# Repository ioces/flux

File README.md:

# Flux - a battery powered soldering station for Weller RT tips

This design is currently a work in progress, with the ultimate goal of being a portable soldering station utilising Weller RT tips. The design has two outputs, and will be powered off regular 18 or 36 V power tool lithium ion battery packs. It will support all RT tips from the RTP, RTM at RTU series.

## Current status

Flux is still a work in progress, and has just made it to the PCA prototyping stage:

- [x] Design
- [x] Schematic capture
- [x] PCB layout of v1.0.0
- [x] Prototype PCB/stencil ordered
- [x] BOM generation
- [x] Part ordering
- [ ] Documentation
- [ ] Prototype assembly
- [ ] Firmware development
- [ ] Prototype testing
- [ ] Enclosure design

## License

This project is licensed under two separate licenses. The hardware design and documentation for this project is licensed under the [CERN Open Hardware Licence Version 2 - Strongly Reciprocal](https://ohwr.org/cern_ohl_s_v2.txt) (CERN-OHL-S-2.0). The software and firmware source code for the project is licensed under the [GNU General Public License Version 3](https://www.gnu.org/licenses/gpl-3.0.txt) (GPL-3.0-only).

Further details can be found in the [license file](LICENSE.md).

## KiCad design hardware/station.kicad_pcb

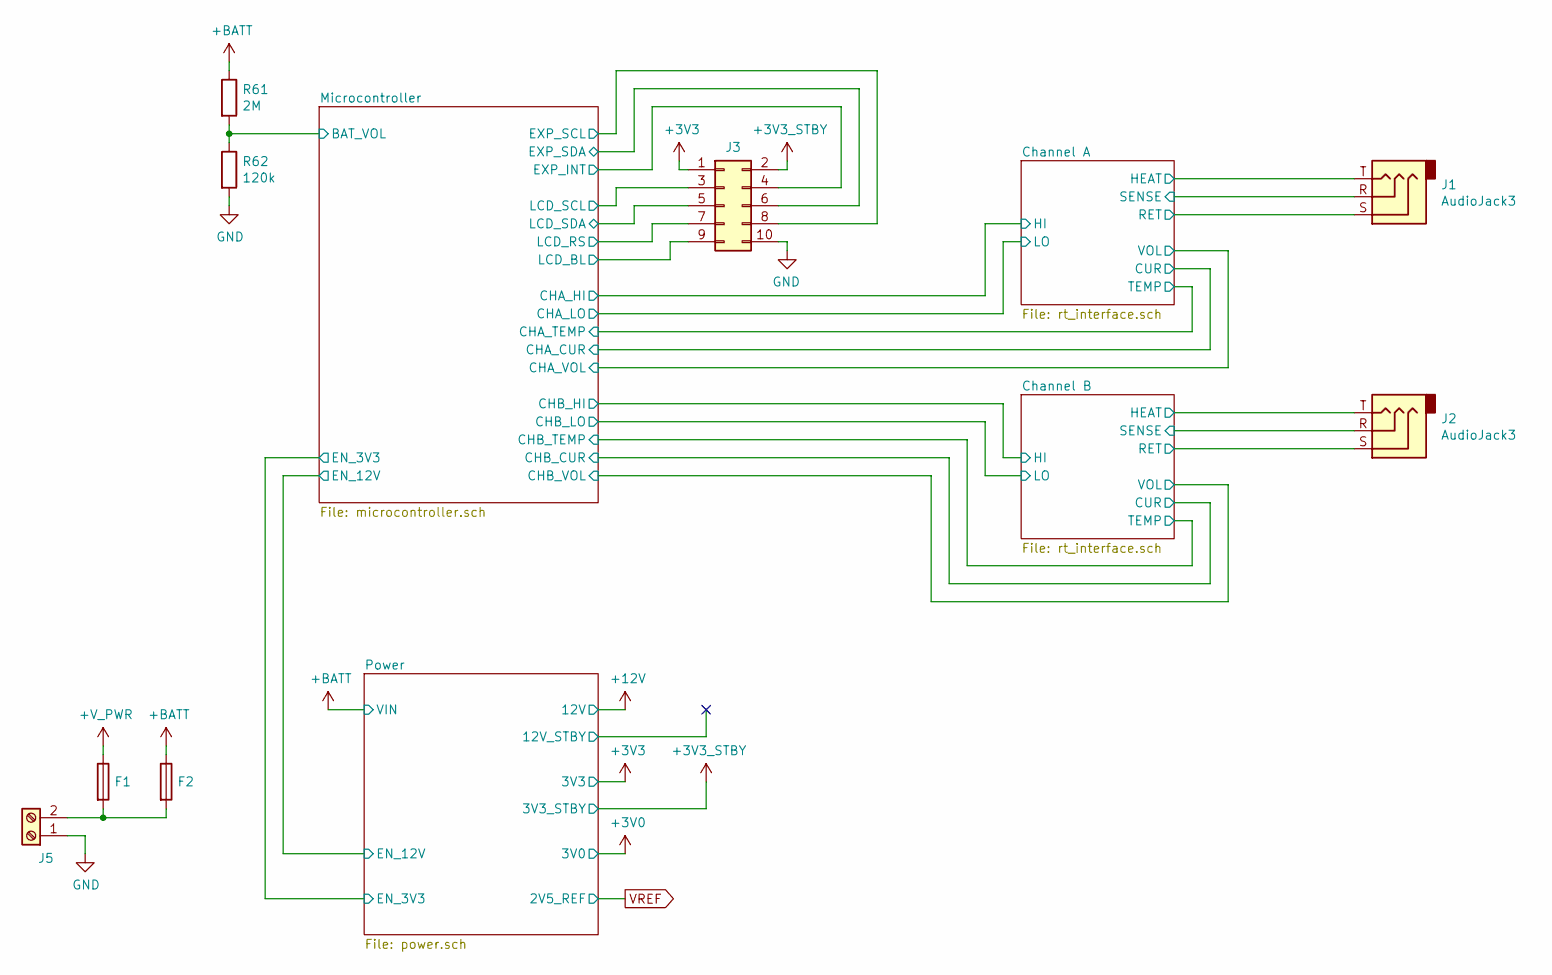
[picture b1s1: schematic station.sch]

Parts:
F1: Fuse; Fuse_2410; Part Number CB61F15A-TR2
F2: Fuse; Fuse_1206_3216Metric; Part Number C1F 375
J1, J2: AudioJack3; Jack_3.5mm_Adam_Tech_ASJ-125-3; Part Number ASJ-125-3
J3: Conn_02x05_Odd_Even; PinHeader_2x05_P2.54mm_BoardEdge; Part Number 10129382-910002BLF
J5: Screw_Terminal_01x02; TerminalBlock_bornier-2_P5.08mm; Part Number TB004-508-02BE
R61: 2M; R_0603_1608Metric; Tolerance 1%; Part Number ERJ-3EKF2004V
R62: 120k; R_0603_1608Metric; Tolerance 1%; Part Number RMCF0603FT120K

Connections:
+3V3: J3.1; also elsewhere on the board
+3V3_STBY: J3.2; also elsewhere on the board
+BATT: F2.1, R61.1; also elsewhere on the board
+V_PWR: F1.1; also elsewhere on the board
/Channel A/HEAT: J1.T; also elsewhere on the board
/Channel A/RET: J1.S; also elsewhere on the board
/Channel A/SENSE: J1.R; also elsewhere on the board
/Channel B/HEAT: J2.T; also elsewhere on the board
/Channel B/RET: J2.S; also elsewhere on the board
/Channel B/SENSE: J2.R; also elsewhere on the board
/Microcontroller/BAT_VOL: R61.2, R62.1; also elsewhere on the board
/Microcontroller/EXP_INT: J3.4; also elsewhere on the board
/Microcontroller/EXP_SCL: J3.8; also elsewhere on the board
/Microcontroller/EXP_SDA: J3.6; also elsewhere on the board
/Microcontroller/LCD_BL: J3.9; also elsewhere on the board
/Microcontroller/LCD_RS: J3.7; also elsewhere on the board
/Microcontroller/LCD_SCL: J3.3; also elsewhere on the board
/Microcontroller/LCD_SDA: J3.5; also elsewhere on the board
GND: J3.10, J5.1, R62.2; also elsewhere on the board
unnamed: F1.2, F2.2, J5.2

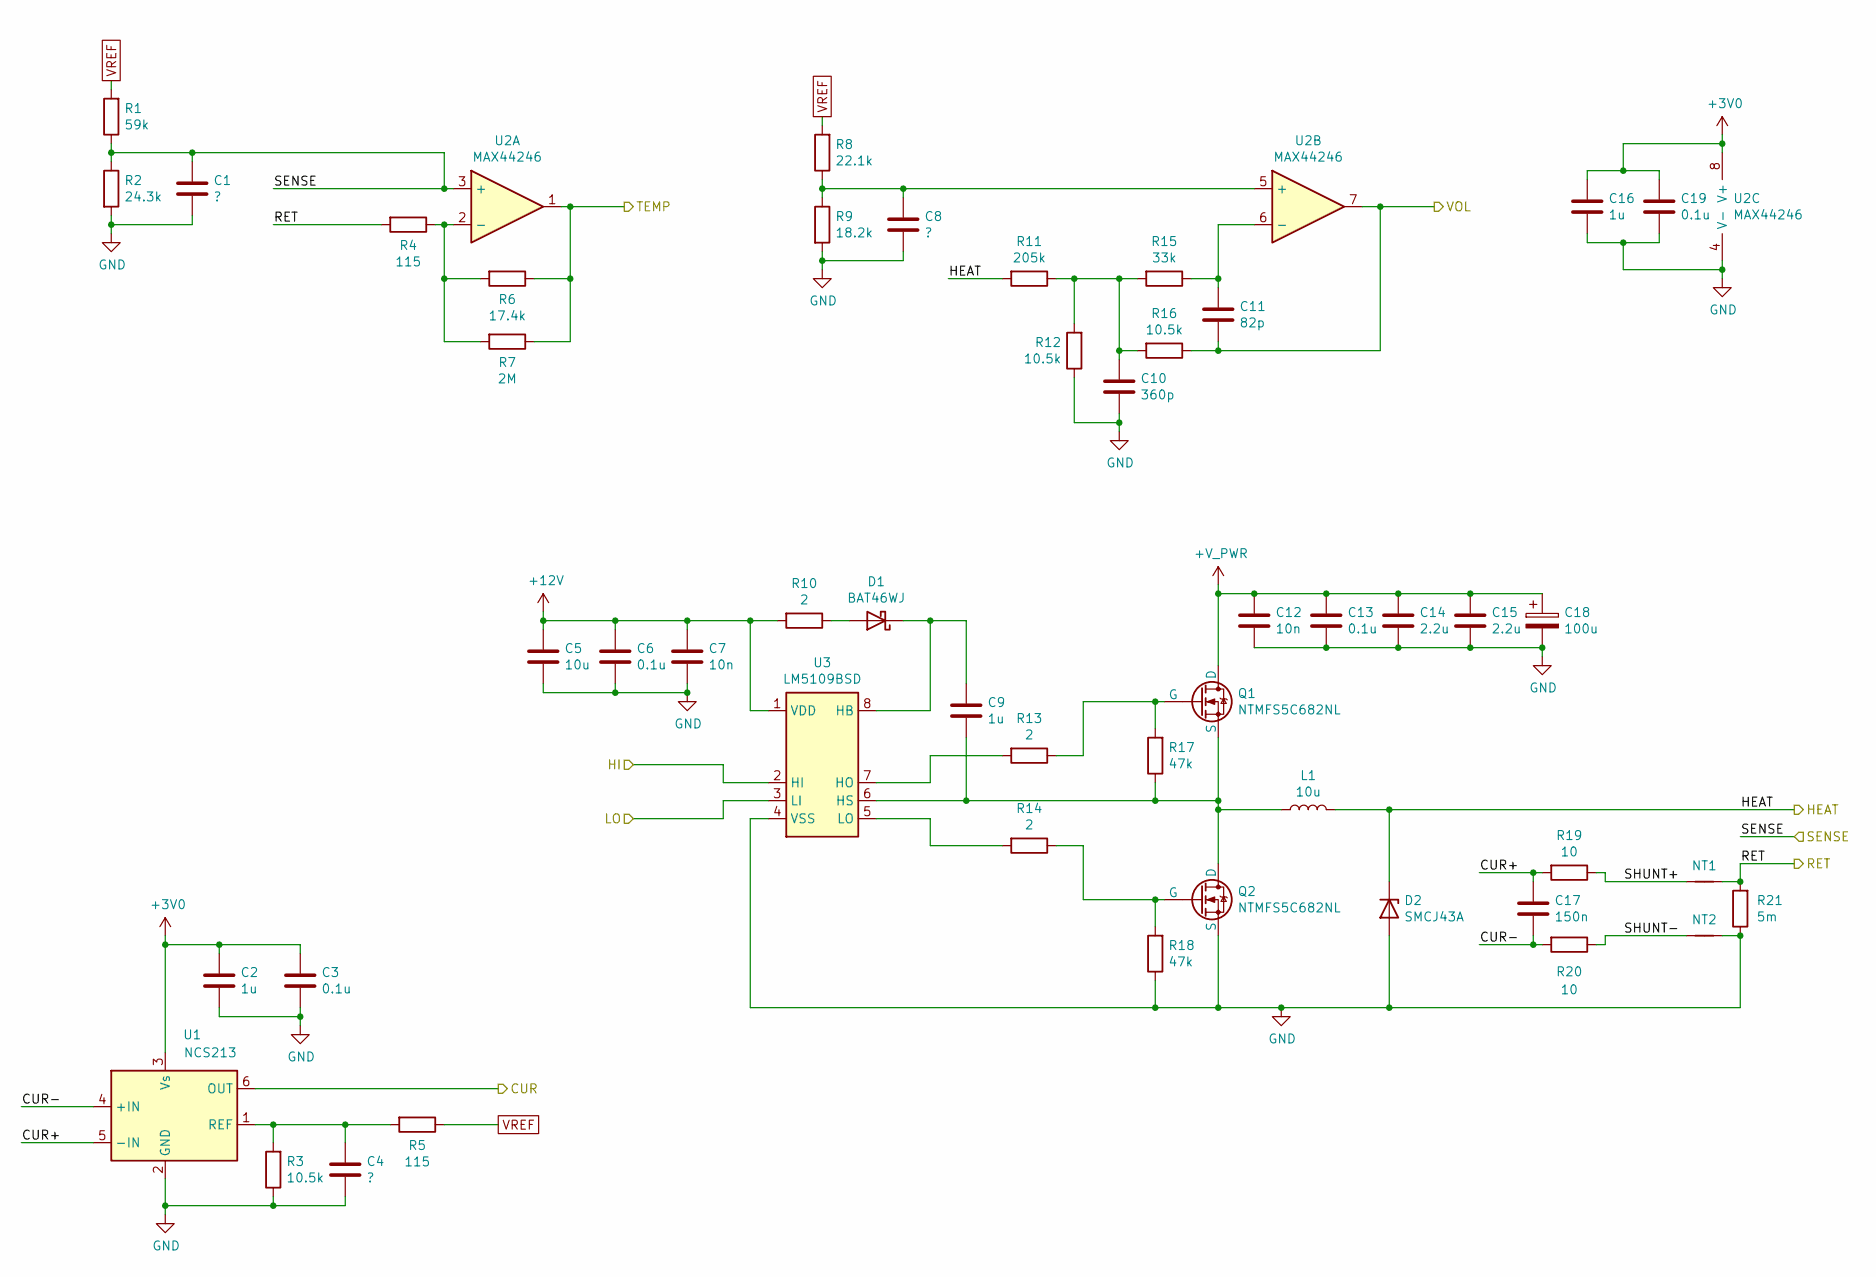
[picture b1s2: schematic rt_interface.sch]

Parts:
C1, C4, C8: ?; C_0805_2012Metric
C2, C9, C16: 1u; C_1206_3216Metric; Voltage Rating 25 V; Tolerance 10%; Part Number C1206C105K3RACAUTO
C3, C6, C19: 0.1u; C_0603_1608Metric; Voltage Rating 35 V; Tolerance 10%; Part Number GMK107B7104KAHT
C5: 10u; C_1206_3216Metric; Voltage Rating 35 V; Tolerance 10%; Part Number GMK316AB7106KL-TR
C7, C12: 10n; C_0603_1608Metric; Voltage Rating 100 V; Tolerance 10%; Part Number C1608X7R2A103K080AA
C10: 360p; C_0603_1608Metric; Voltage Rating 50 V; Tolerance 5%; Part Number C0603C361J5GAC7867
C11: 82p; C_0603_1608Metric; Voltage Rating 50 V; Tolerance 5%; Part Number C0603C820J5GACTU
C13: 0.1u; C_0805_2012Metric; Voltage Rating 100 V; Tolerance 10%; Part Number 885012207128
C14, C15: 2.2u; C_1210_3225Metric; Voltage Rating 100 V; Tolerance 10%; Part Number HMK325B7225KM-T
C17: 150n; C_0603_1608Metric; Voltage Rating 25 V; Tolerance 10%; Part Number 885012206072
C18: 100u; CP_Radial_D10.0mm_P5.00mm; Voltage Rating 63 V; Tolerance 20%; Part Number 63YXJ100M10X12.5
D1: BAT46WJ; D_SOD-323F; Part Number BAT46WJF
D2: SMCJ43A; D_SMC; Part Number SMCJ43A
L1: 10u; L_Bourns_SRP1265C; Part Number SRP1265C-100M
NT1, NT2: Net-Tie_2; NetTie-2_SMD_Pad0.2mm
Q1, Q2: NTMFS5C682NL; ONSemi_SO-8FL_488AA_Fill; Part Number NTMFS5C682NL
R1: 59k; R_0603_1608Metric; Tolerance 1%; Part Number RMCF0603FT59K0
R2: 24.3k; R_0603_1608Metric; Tolerance 1%; Part Number RMCF0603FT24K3
R3, R12, R16: 10.5k; R_0603_1608Metric; Tolerance 1%; Part Number RMCF0603FT10K5
R4, R5: 115; R_0603_1608Metric; Tolerance 1%; Part Number RMCF0603FT115R
R6: 17.4k; R_0603_1608Metric; Tolerance 1%; Part Number RMCF0603FT17K4
R7: 2M; R_0603_1608Metric; Tolerance 1%; Part Number ERJ-3EKF2004V
R8: 22.1k; R_0603_1608Metric; Tolerance 1%; Part Number RMCF0603FT22K1
R9: 18.2k; R_0603_1608Metric; Tolerance 1%; Part Number RMCF0603FT18K2
R10, R13, R14: 2; R_0603_1608Metric; Tolerance 5%; Part Number ERJ-PA3J2R0V
R11: 205k; R_0603_1608Metric; Tolerance 1%; Part Number RMCF0603FT205K
R15: 33k; R_0603_1608Metric; Tolerance 1%; Part Number CR0603-FX-3302ELF
R17, R18: 47k; R_0603_1608Metric; Tolerance 5%; Part Number CR0603-JW-473ELF
R19, R20: 10; R_0603_1608Metric; Tolerance 1%; Part Number CR0603-FX-10R0ELF
R21: 5m; R_0612_1632Metric; Tolerance 1%; Part Number CSRF0612FT5L00
U1: NCS213; SOT-363_SC-70-6; Part Number NCS213RSQT2G
U2: MAX44246; MSOP-8_3x3mm_P0.65mm; Part Number MAX44246AUA+
U3: LM5109BSD; WSON-8_4x4mm_P0.8mm; Part Number LM5109BSD/NOPB

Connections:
+3V0: C2.1, C3.1, C16.1, C19.1, U1.3 (Vs), U2.8 (V+); also elsewhere on the board
+12V: C5.1, C6.1, C7.1, R10.2, U3.1 (VDD); also elsewhere on the board
+V_PWR: C12.1, C13.1, C14.1, C15.1, C18.1, Q1.5 (D); also elsewhere on the board
/Channel A/CUR+: C17.1, R19.2, U1.5 (-IN)
/Channel A/CUR-: C17.2, R20.2, U1.4 (+IN)
/Channel A/HEAT: D2.1 (K), L1.2, R11.2; also elsewhere on the board
/Channel A/RET: NT1.2, R4.2, R21.2; also elsewhere on the board
/Channel A/SENSE: C1.2, R1.1, R2.1, U2.3 (+); also elsewhere on the board
/Channel A/SHUNT+: NT1.1, R19.1
/Channel A/SHUNT-: NT2.1, R20.1
/Microcontroller/CHA_CUR: U1.6 (OUT); also elsewhere on the board
/Microcontroller/CHA_HI: U3.2 (HI); also elsewhere on the board
/Microcontroller/CHA_LO: U3.3 (LI); also elsewhere on the board
/Microcontroller/CHA_TEMP: R6.1, R7.1, U2.1; also elsewhere on the board
/Microcontroller/CHA_VOL: C11.2, R16.1, U2.7; also elsewhere on the board
GND: C1.1, C2.2, C3.2, C4.1, C5.2, C6.2, C7.2, C8.1, C10.2, C12.2, C13.2, C14.2, C15.2, C16.2, C18.2, C19.2, D2.2 (A), NT2.2, Q2.1 (S), Q2.2 (S), Q2.3 (S), R2.2, R3.1, R9.2, R12.1, R18.1, R21.1, U1.2 (GND), U2.4 (V-), U3.4 (VSS), U3.9 (VSS); also elsewhere on the board
unnamed: C4.2, R3.2, R5.2, U1.1 (REF)
unnamed: C8.2, R8.1, R9.1, U2.5 (+)
unnamed: C9.1, L1.1, Q1.1 (S), Q1.2 (S), Q1.3 (S), Q2.5 (D), R17.1, U3.6 (HS)
unnamed: C9.2, D1.1 (K), U3.8 (HB)
unnamed: C10.1, R11.1, R12.2, R15.2, R16.2
unnamed: C11.1, R15.1, U2.6 (-)
unnamed: D1.2 (A), R10.1
unnamed: Q1.4 (G), R13.1, R17.2
unnamed: Q2.4 (G), R14.1, R18.2
unnamed: R4.1, R6.2, R7.2, U2.2 (-)
unnamed: R13.2, U3.7 (HO)
unnamed: R14.2, U3.5 (LO)
VREF: R1.2, R5.1, R8.2; also elsewhere on the board

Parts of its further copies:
C38, C41, C45: ?; C_0805_2012Metric
C39, C46, C53: 1u; C_1206_3216Metric; Voltage Rating 25 V; Tolerance 10%; Part Number C1206C105K3RACAUTO
C40, C43, C56: 0.1u; C_0603_1608Metric; Voltage Rating 35 V; Tolerance 10%; Part Number GMK107B7104KAHT
C42: 10u; C_1206_3216Metric; Voltage Rating 35 V; Tolerance 10%; Part Number GMK316AB7106KL-TR
C44, C49: 10n; C_0603_1608Metric; Voltage Rating 100 V; Tolerance 10%; Part Number C1608X7R2A103K080AA
C47: 360p; C_0603_1608Metric; Voltage Rating 50 V; Tolerance 5%; Part Number C0603C361J5GAC7867
C48: 82p; C_0603_1608Metric; Voltage Rating 50 V; Tolerance 5%; Part Number C0603C820J5GACTU
C50: 0.1u; C_0805_2012Metric; Voltage Rating 100 V; Tolerance 10%; Part Number 885012207128
C51, C52: 2.2u; C_1210_3225Metric; Voltage Rating 100 V; Tolerance 10%; Part Number HMK325B7225KM-T
C54: 150n; C_0603_1608Metric; Voltage Rating 25 V; Tolerance 10%; Part Number 885012206072
C55: 100u; CP_Radial_D10.0mm_P5.00mm; Voltage Rating 63 V; Tolerance 20%; Part Number 63YXJ100M10X12.5
D3: BAT46WJ; D_SOD-323F; Part Number BAT46WJF
D4: SMCJ43A; D_SMC; Part Number SMCJ43A
L4: 10u; L_Bourns_SRP1265C; Part Number SRP1265C-100M
NT3, NT4: Net-Tie_2; NetTie-2_SMD_Pad0.2mm
Q7, Q8: NTMFS5C682NL; ONSemi_SO-8FL_488AA_Fill; Part Number NTMFS5C682NL
R37: 59k; R_0603_1608Metric; Tolerance 1%; Part Number RMCF0603FT59K0
R38: 24.3k; R_0603_1608Metric; Tolerance 1%; Part Number RMCF0603FT24K3
R39, R48, R52: 10.5k; R_0603_1608Metric; Tolerance 1%; Part Number RMCF0603FT10K5
R40, R41: 115; R_0603_1608Metric; Tolerance 1%; Part Number RMCF0603FT115R
R42: 17.4k; R_0603_1608Metric; Tolerance 1%; Part Number RMCF0603FT17K4
R43: 2M; R_0603_1608Metric; Tolerance 1%; Part Number ERJ-3EKF2004V
R44: 22.1k; R_0603_1608Metric; Tolerance 1%; Part Number RMCF0603FT22K1
R45: 18.2k; R_0603_1608Metric; Tolerance 1%; Part Number RMCF0603FT18K2
R46, R49, R50: 2; R_0603_1608Metric; Tolerance 5%; Part Number ERJ-PA3J2R0V
R47: 205k; R_0603_1608Metric; Tolerance 1%; Part Number RMCF0603FT205K
R51: 33k; R_0603_1608Metric; Tolerance 1%; Part Number CR0603-FX-3302ELF
R53, R54: 47k; R_0603_1608Metric; Tolerance 5%; Part Number CR0603-JW-473ELF
R55, R56: 10; R_0603_1608Metric; Tolerance 1%; Part Number CR0603-FX-10R0ELF
R57: 5m; R_0612_1632Metric; Tolerance 1%; Part Number CSRF0612FT5L00
U8: NCS213; SOT-363_SC-70-6; Part Number NCS213RSQT2G
U9: MAX44246; MSOP-8_3x3mm_P0.65mm; Part Number MAX44246AUA+
U10: LM5109BSD; WSON-8_4x4mm_P0.8mm; Part Number LM5109BSD/NOPB

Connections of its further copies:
+3V0: C39.1, C40.1, C53.1, C56.1, U8.3 (Vs), U9.8 (V+); also elsewhere on the board
+12V: C42.1, C43.1, C44.1, R46.2, U10.1 (VDD); also elsewhere on the board
+V_PWR: C49.1, C50.1, C51.1, C52.1, C55.1, Q7.5 (D); also elsewhere on the board
/Channel B/CUR+: C54.1, R55.2, U8.5 (-IN)
/Channel B/CUR-: C54.2, R56.2, U8.4 (+IN)
/Channel B/HEAT: D4.1 (K), L4.2, R47.2; also elsewhere on the board
/Channel B/RET: NT3.2, R40.2, R57.2; also elsewhere on the board
/Channel B/SENSE: C38.2, R37.1, R38.1, U9.3 (+); also elsewhere on the board
/Channel B/SHUNT+: NT3.1, R55.1
/Channel B/SHUNT-: NT4.1, R56.1
/Microcontroller/CHB_CUR: U8.6 (OUT); also elsewhere on the board
/Microcontroller/CHB_HI: U10.2 (HI); also elsewhere on the board
/Microcontroller/CHB_LO: U10.3 (LI); also elsewhere on the board
/Microcontroller/CHB_TEMP: R42.1, R43.1, U9.1; also elsewhere on the board
/Microcontroller/CHB_VOL: C48.2, R52.1, U9.7; also elsewhere on the board
GND: C38.1, C39.2, C40.2, C41.1, C42.2, C43.2, C44.2, C45.1, C47.2, C49.2, C50.2, C51.2, C52.2, C53.2, C55.2, C56.2, D4.2 (A), NT4.2, Q8.1 (S), Q8.2 (S), Q8.3 (S), R38.2, R39.1, R45.2, R48.1, R54.1, R57.1, U8.2 (GND), U9.4 (V-), U10.4 (VSS), U10.9 (VSS); also elsewhere on the board
unnamed: C41.2, R39.2, R41.2, U8.1 (REF)
unnamed: C45.2, R44.1, R45.1, U9.5 (+)
unnamed: C46.1, L4.1, Q7.1 (S), Q7.2 (S), Q7.3 (S), Q8.5 (D), R53.1, U10.6 (HS)
unnamed: C46.2, D3.1 (K), U10.8 (HB)
unnamed: C47.1, R47.1, R48.2, R51.2, R52.2
unnamed: C48.1, R51.1, U9.6 (-)
unnamed: D3.2 (A), R46.1
unnamed: Q7.4 (G), R49.1, R53.2
unnamed: Q8.4 (G), R50.1, R54.2
unnamed: R40.1, R42.2, R43.2, U9.2 (-)
unnamed: R49.2, U10.7 (HO)
unnamed: R50.2, U10.5 (LO)
VREF: R37.2, R41.1, R44.2; also elsewhere on the board

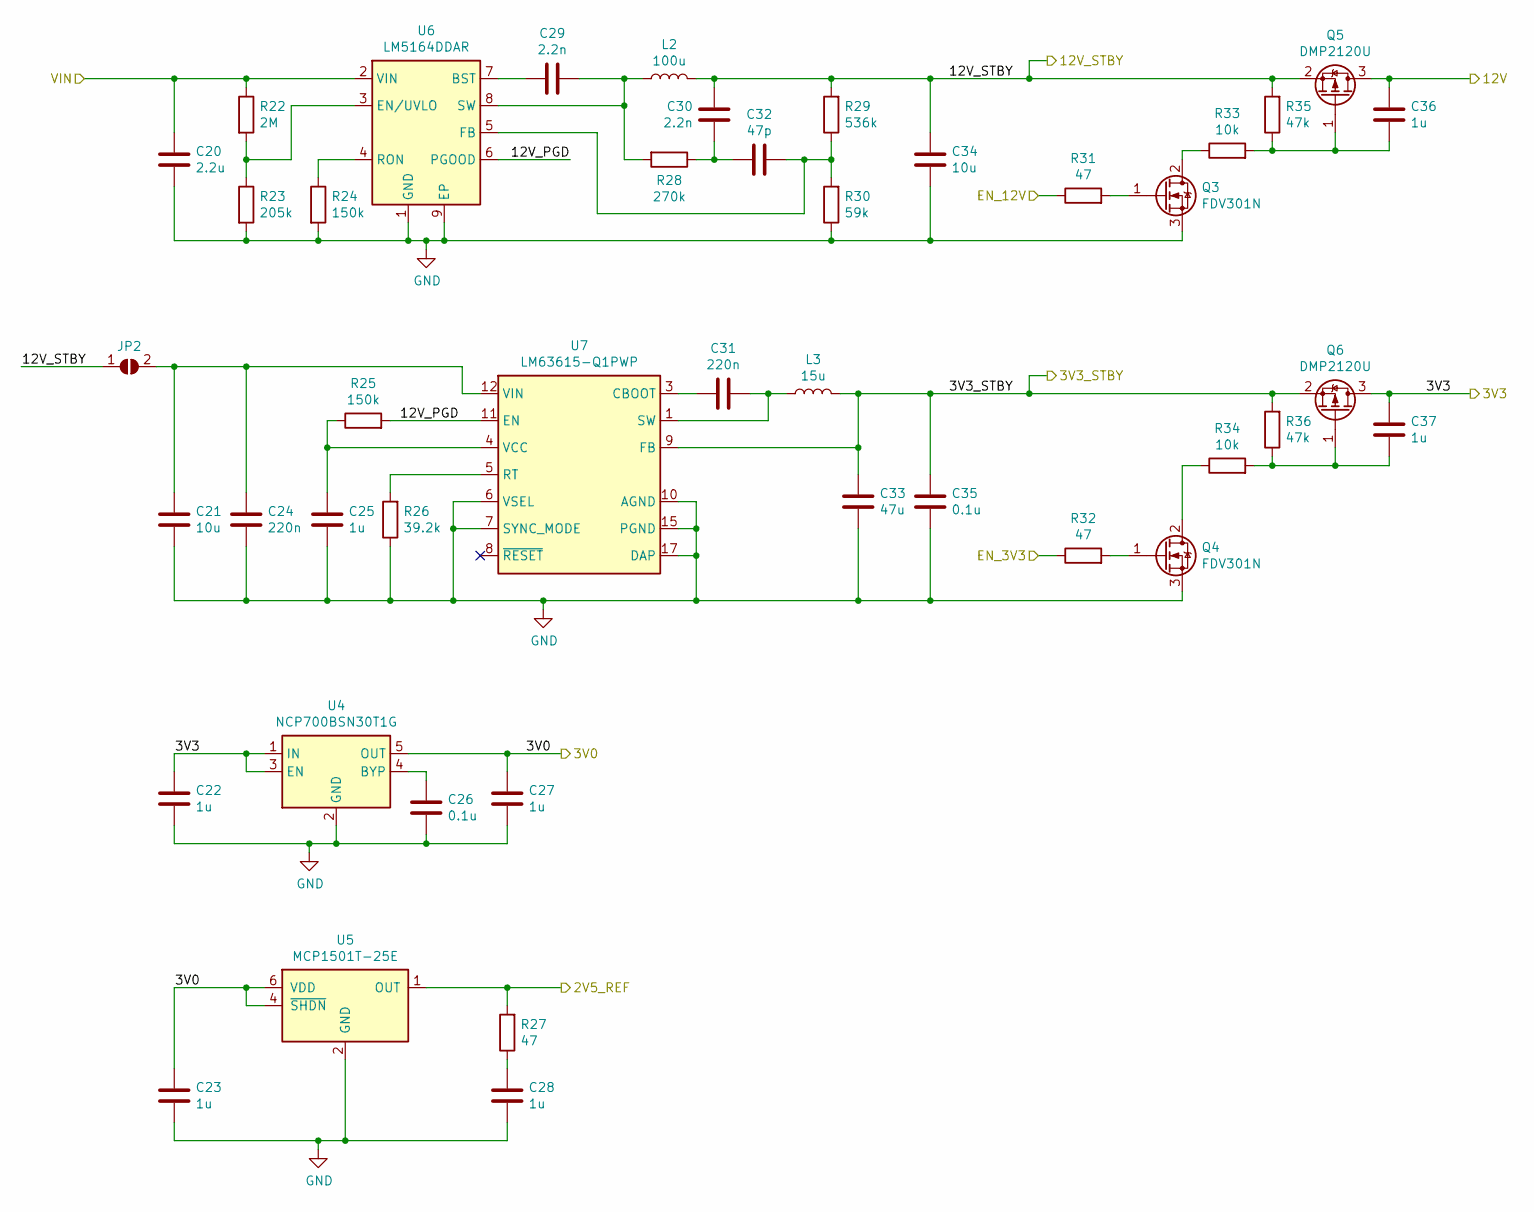
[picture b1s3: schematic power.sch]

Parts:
C20: 2.2u; C_1210_3225Metric; Voltage Rating 100 V; Tolerance 10%; Part Number HMK325B7225KM-T
C21, C34: 10u; C_1206_3216Metric; Voltage Rating 35 V; Tolerance 10%; Part Number GMK316AB7106KL-TR
C22, C23, C25, C27, C28, C36, C37: 1u; C_1206_3216Metric; Voltage Rating 25 V; Tolerance 10%; Part Number C1206C105K3RACAUTO
C24, C31: 220n; C_0603_1608Metric; Voltage Rating 50 V; Tolerance 10%; Part Number C1608X7R1H224K080AB
C26, C35: 0.1u; C_0603_1608Metric; Voltage Rating 35 V; Tolerance 10%; Part Number GMK107B7104KAHT
C29, C30: 2.2n; C_0805_2012Metric; Voltage Rating 50 V; Tolerance 10%; Part Number C0805C222K5RACTU
C32: 47p; C_0603_1608Metric; Tolerance 5%; Voltage Rating 16V; Part Number 885012006021
C33: 47u; C_1210_3225Metric; Voltage Rating 16 V; Tolerance 10%; Part Number GRM32EC81C476KE15K
JP2: SolderJumper_2_Open; SolderJumper-2_3A
L2: 100u; L_Coilcraft_MSS1210; Part Number MSS1210-104KEB
L3: 15u; L_TDK_SLF10165; Part Number SLF10165T-150M3R13PF
Q3, Q4: FDV301N; SOT-23; Part Number FDV301N
Q5, Q6: DMP2120U; SOT-23; Part Number DMP2120U
R22: 2M; R_0603_1608Metric; Tolerance 1%; Part Number ERJ-3EKF2004V
R23: 205k; R_0603_1608Metric; Tolerance 1%; Part Number RMCF0603FT205K
R24, R25: 150k; R_0603_1608Metric; Tolerance 1%; Part Number RMCF0603FT150K
R26: 39.2k; R_0603_1608Metric; Tolerance 1%; Part Number RMCF0603FT39K2
R27, R31, R32: 47; R_0603_1608Metric; Tolerance 1%; Part Number RMCF0603FT47R0
R28: 270k; R_0603_1608Metric; Tolerance 1%; Part Number RMCF0603FT270K
R29: 536k; R_0603_1608Metric; Tolerance 1%; Part Number RMCF0603FT536K
R30: 59k; R_0603_1608Metric; Tolerance 1%; Part Number RMCF0603FT59K0
R33, R34: 10k; R_0603_1608Metric; Tolerance 5%; Part Number RMCF0603JG10K0
R35, R36: 47k; R_0603_1608Metric; Tolerance 5%; Part Number CR0603-JW-473ELF
U4: NCP700BSN30T1G; SOT-23-5; Part Number NCP700BSN30T1G
U5: MCP1501T-25E; SOT-23-6; Part Number MCP1501T-25E/CHY
U6: LM5164DDAR; TI_SO-PowerPAD-8; Part Number LM5164DDAR
U7: LM63615-Q1PWP; HTSSOP-16-1EP_4.4x5mm_P0.65mm_EP3.4x5mm_Mask2.46x2.31mm; Part Number LM63615-Q1PWP

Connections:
+3V0: C23.1, C27.1, U4.5 (OUT), U5.4 (~SHDN), U5.6 (VDD); also elsewhere on the board
+3V3: C22.1, C37.1, Q6.3 (D), U4.1 (IN), U4.3 (EN); also elsewhere on the board
+3V3_STBY: C33.1, C35.1, L3.2, Q6.2 (S), R36.2, U7.9 (FB); also elsewhere on the board
+12V: C36.1, Q5.3 (D); also elsewhere on the board
+BATT: C20.1, R22.1, U6.2 (VIN); also elsewhere on the board
/Microcontroller/EN_3V3: R32.1; also elsewhere on the board
/Microcontroller/EN_12V: R31.1; also elsewhere on the board
/Power/12V_PGD: R25.2, U6.6 (PGOOD), U7.11 (EN)
/Power/12V_STBY: C30.2, C34.1, JP2.1 (A), L2.2, Q5.2 (S), R29.2, R35.2
GND: C20.2, C21.2, C22.2, C23.2, C24.2, C25.2, C26.2, C27.2, C28.2, C33.2, C34.2, C35.2, Q3.3 (S), Q4.3 (S), R23.2, R24.2, R26.1, R30.1, U4.2 (GND), U5.2 (GND), U5.3 (GND), U5.5 (GND), U6.1 (GND), U6.9 (EP), U7.6 (VSEL), U7.7 (SYNC_MODE), U7.10 (AGND), U7.15 (PGND), U7.16 (PGND), U7.17 (DAP); also elsewhere on the board
unnamed: C21.1, C24.1, JP2.2 (B), U7.12 (VIN), U7.13 (VIN)
unnamed: C25.1, R25.1, U7.4 (VCC)
unnamed: C26.1, U4.4 (BYP)
unnamed: C28.1, R27.1
unnamed: C29.1, L2.1, R28.2, U6.8 (SW)
unnamed: C29.2, U6.7 (BST)
unnamed: C30.1, C32.1, R28.1
unnamed: C31.1, L3.1, U7.1 (SW), U7.2 (SW)
unnamed: C31.2, U7.3 (CBOOT)
unnamed: C32.2, R29.1, R30.2, U6.5 (FB)
unnamed: C36.2, Q5.1 (G), R33.2, R35.1
unnamed: C37.2, Q6.1 (G), R34.2, R36.1
unnamed: Q3.1 (G), R31.2
unnamed: Q3.2 (D), R33.1
unnamed: Q4.1 (G), R32.2
unnamed: Q4.2 (D), R34.1
unnamed: R22.2, R23.1, U6.3 (EN/UVLO)
unnamed: R24.1, U6.4 (RON)
unnamed: R26.2, U7.5 (RT)
VREF: R27.2, U5.1 (OUT); also elsewhere on the board

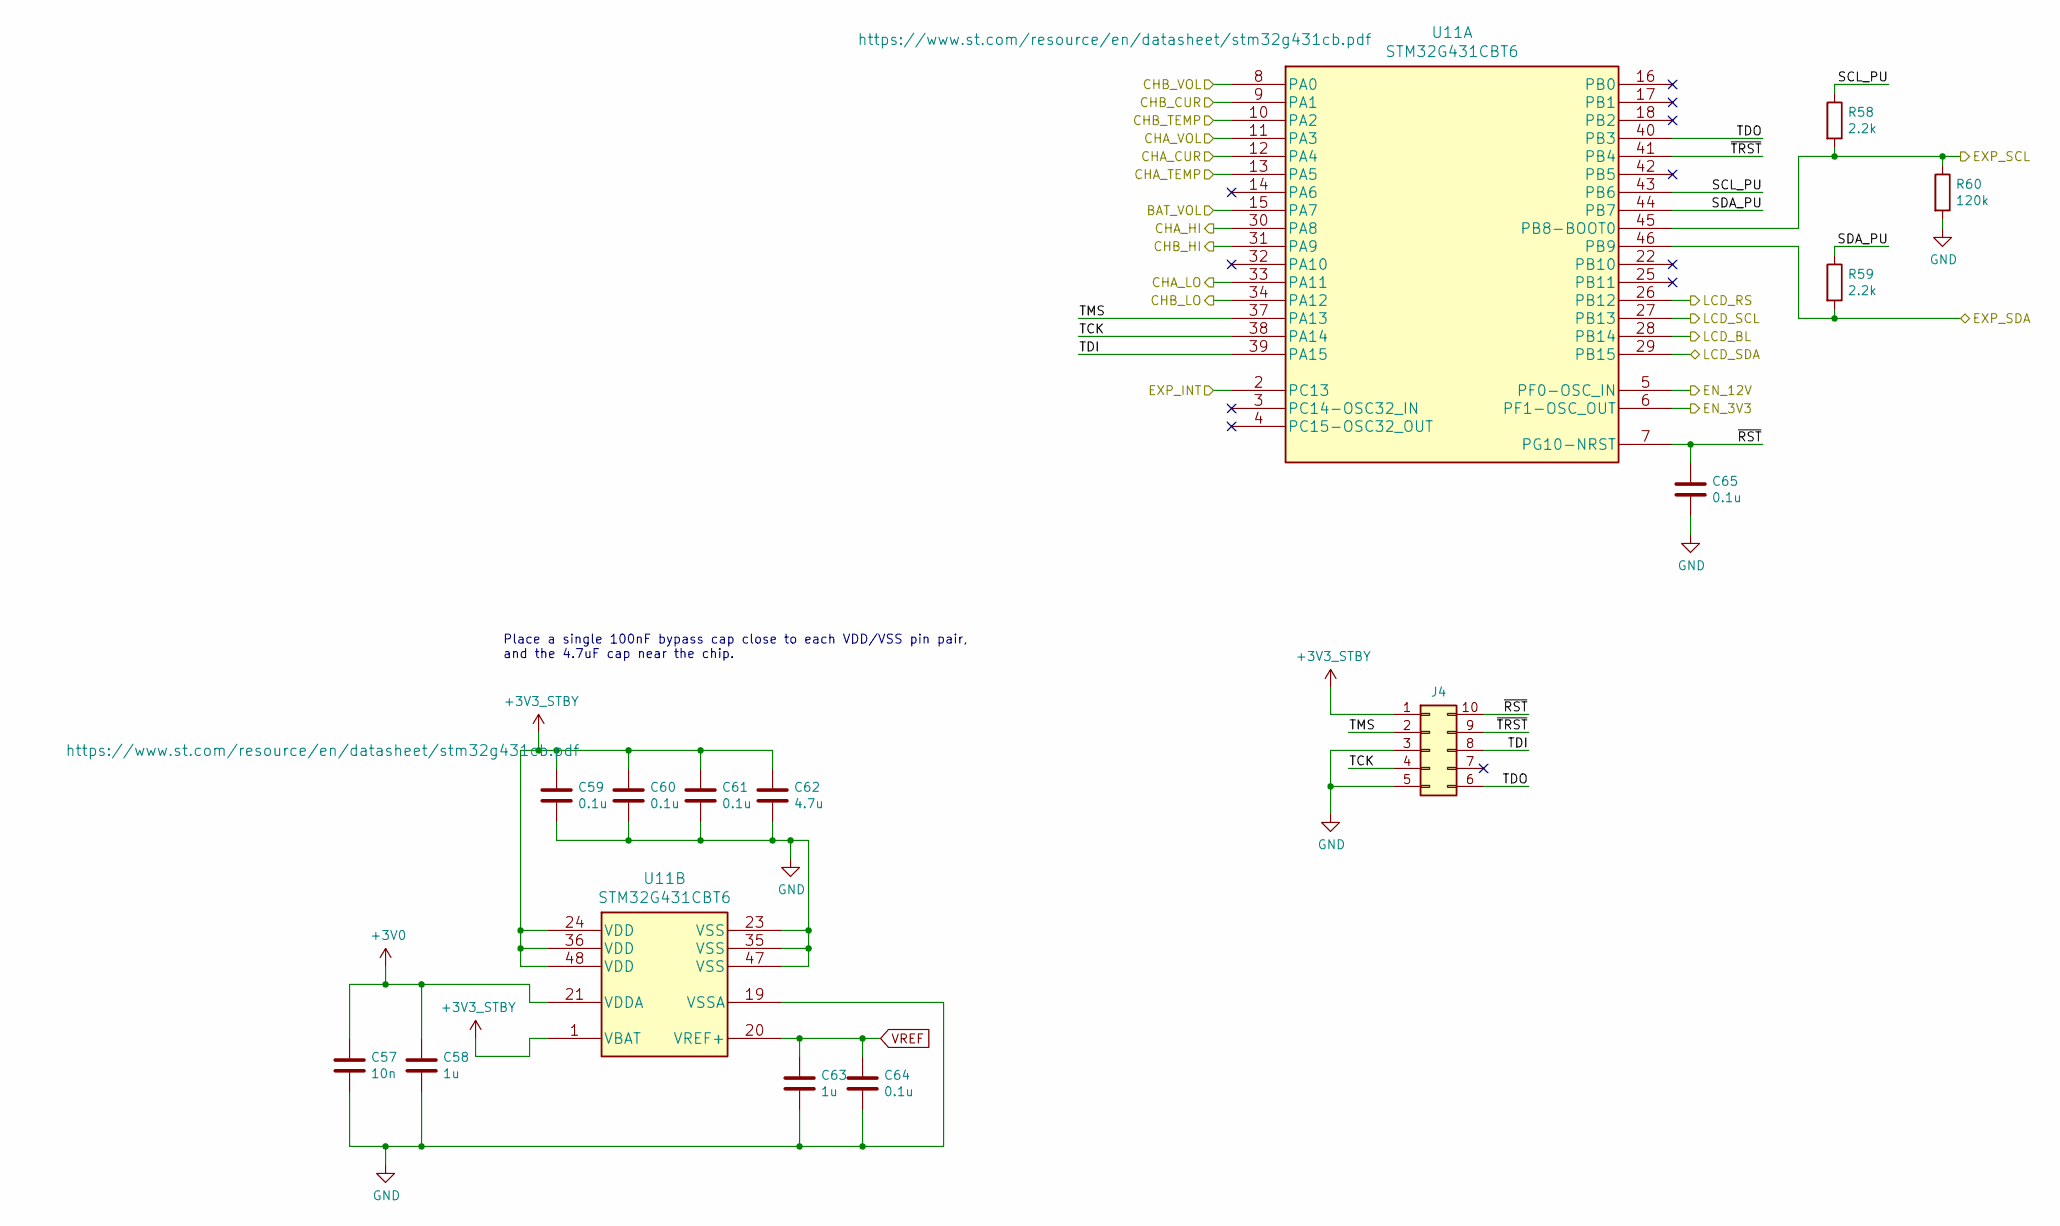
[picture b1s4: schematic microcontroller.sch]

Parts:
C57: 10n; C_0603_1608Metric; Voltage Rating 100 V; Tolerance 10%; Part Number C1608X7R2A103K080AA
C58, C63: 1u; C_1206_3216Metric; Voltage Rating 25 V; Tolerance 10%; Part Number C1206C105K3RACAUTO
C59, C60, C61, C64, C65: 0.1u; C_0603_1608Metric; Voltage Rating 35 V; Tolerance 10%; Part Number GMK107B7104KAHT
C62: 4.7u; C_1206_3216Metric; Voltage Rating 25 V; Tolerance 10%; Part Number CL31B475KAHNFNE
J4: Conn_02x05_Counter_Clockwise; Tag-Connect_TC2050-IDC-NL_2x05_P1.27mm_Vertical
R58, R59: 2.2k; R_0603_1608Metric; Tolerance 5%; Part Number RMCF0603JT2K20
R60: 120k; R_0603_1608Metric; Tolerance 1%; Part Number RMCF0603FT120K
U11: STM32G431CBT6; LQFP-48_7x7mm_P0.5mm; Part Number STM32G431CBT6

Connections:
+3V0: C57.1, C58.1, U11.21 (VDDA); also elsewhere on the board
+3V3_STBY: C59.1, C60.1, C61.1, C62.1, J4.1, U11.1 (VBAT), U11.24 (VDD), U11.36 (VDD), U11.48 (VDD); also elsewhere on the board
/Microcontroller/BAT_VOL: U11.15 (PA7); also elsewhere on the board
/Microcontroller/CHA_CUR: U11.12 (PA4); also elsewhere on the board
/Microcontroller/CHA_HI: U11.30 (PA8); also elsewhere on the board
/Microcontroller/CHA_LO: U11.33 (PA11); also elsewhere on the board
/Microcontroller/CHA_TEMP: U11.13 (PA5); also elsewhere on the board
/Microcontroller/CHA_VOL: U11.11 (PA3); also elsewhere on the board
/Microcontroller/CHB_CUR: U11.9 (PA1); also elsewhere on the board
/Microcontroller/CHB_HI: U11.31 (PA9); also elsewhere on the board
/Microcontroller/CHB_LO: U11.34 (PA12); also elsewhere on the board
/Microcontroller/CHB_TEMP: U11.10 (PA2); also elsewhere on the board
/Microcontroller/CHB_VOL: U11.8 (PA0); also elsewhere on the board
/Microcontroller/EN_3V3: U11.6 (PF1-OSC_OUT); also elsewhere on the board
/Microcontroller/EN_12V: U11.5 (PF0-OSC_IN); also elsewhere on the board
/Microcontroller/EXP_INT: U11.2 (PC13); also elsewhere on the board
/Microcontroller/EXP_SCL: R58.2, R60.1, U11.45 (PB8-BOOT0); also elsewhere on the board
/Microcontroller/EXP_SDA: R59.2, U11.46 (PB9); also elsewhere on the board
/Microcontroller/LCD_BL: U11.28 (PB14); also elsewhere on the board
/Microcontroller/LCD_RS: U11.26 (PB12); also elsewhere on the board
/Microcontroller/LCD_SCL: U11.27 (PB13); also elsewhere on the board
/Microcontroller/LCD_SDA: U11.29 (PB15); also elsewhere on the board
/Microcontroller/SCL_PU: R58.1, U11.43 (PB6)
/Microcontroller/SDA_PU: R59.1, U11.44 (PB7)
/Microcontroller/TCK: J4.4, U11.38 (PA14)
/Microcontroller/TDI: J4.8, U11.39 (PA15)
/Microcontroller/TDO: J4.6, U11.40 (PB3)
/Microcontroller/TMS: J4.2, U11.37 (PA13)
/Microcontroller/~RST: C65.1, J4.10, U11.7 (PG10-NRST)
/Microcontroller/~TRST: J4.9, U11.41 (PB4)
GND: C57.2, C58.2, C59.2, C60.2, C61.2, C62.2, C63.2, C64.2, C65.2, J4.3, J4.5, R60.2, U11.19 (VSSA), U11.23 (VSS), U11.35 (VSS), U11.47 (VSS); also elsewhere on the board
VREF: C63.1, C64.1, U11.20 (VREF+); also elsewhere on the board

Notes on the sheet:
Place a single 100nF bypass cap close to each VDD/VSS pin pair, and the 4.7uF cap near the chip.

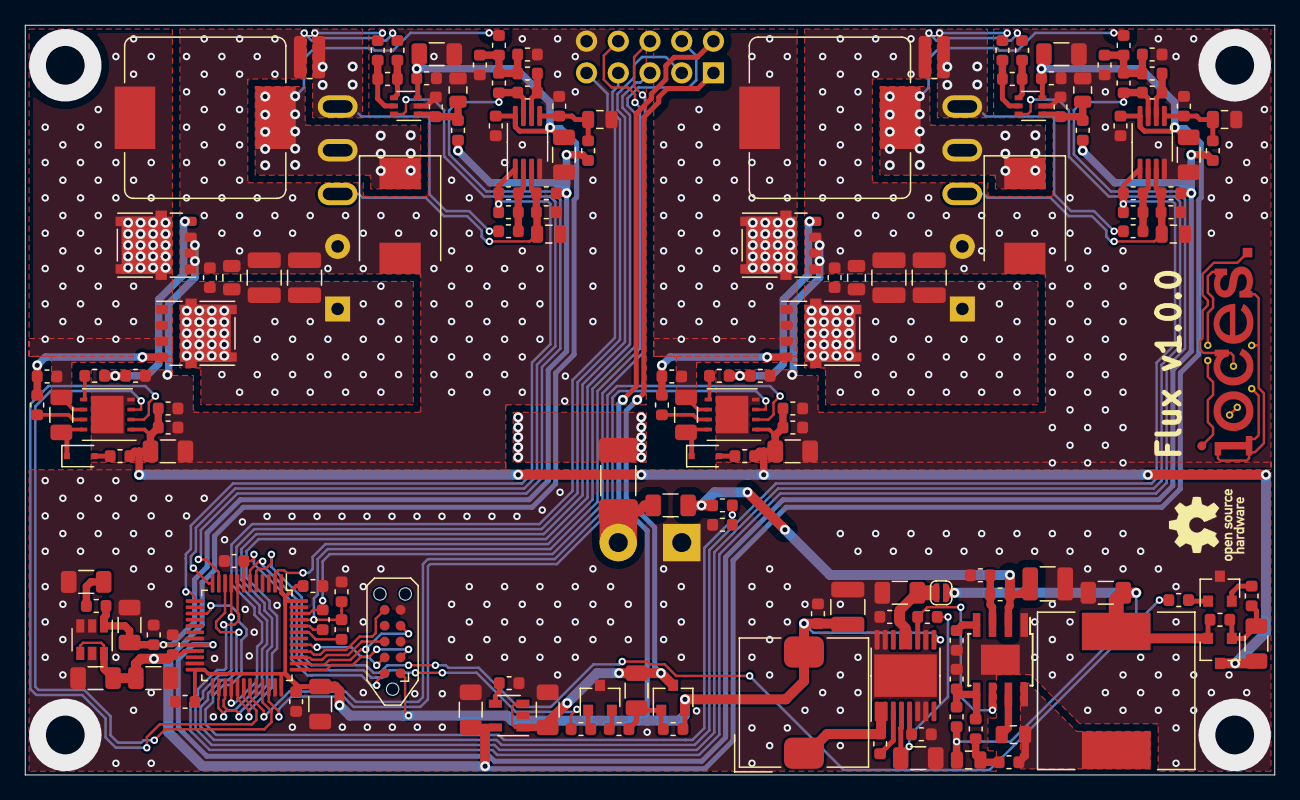
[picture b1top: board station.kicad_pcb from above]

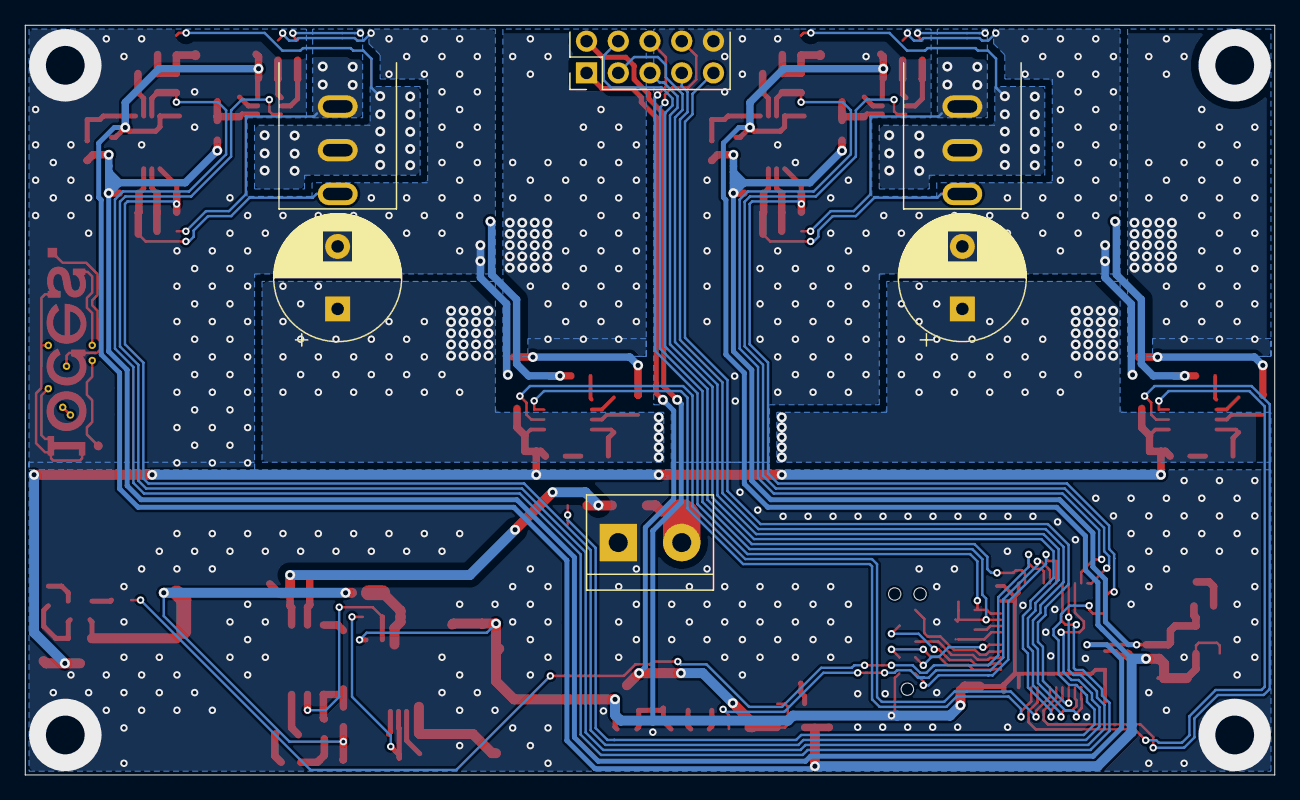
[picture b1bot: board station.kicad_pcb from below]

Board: 2 copper layers, 100.0 x 60.0 mm, 167 parts (10 on the bottom side), 96 nets.

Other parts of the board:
Ref**: Val**; IocesLogo

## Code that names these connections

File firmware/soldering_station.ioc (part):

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PB13.GPIOParameters=GPIO_Label
Mcu.UserName=STM32G431CBTx
PB14.GPIO_Label=LCD_BL
PA0.GPIO_Label=CHB_VOL
PA12.GPIOParameters=GPIO_Label
PA9.GPIOParameters=GPIO_Label
PA11.GPIOParameters=GPIO_Label
PA11.Mode=PWM Generation1 CH1 CH1N
PA3.GPIOParameters=GPIO_Label
PB6.GPIO_Label=SCL_PU
PC13.GPIO_Label=EXP_INT
PB13.GPIO_Label=LCD_SCL (SCK)
PB13.Signal=SPI2_SCK
PB15.Signal=SPI2_MOSI
PA2.GPIOParameters=GPIO_Label
RCC.SYSCLKSource=RCC_SYSCLKSOURCE_PLLCLK
PA12.Signal=TIM1_CH2N
PA4.Mode=IN17-Single-Ended
PB6.Signal=GPIO_Output
PA8.GPIOParameters=GPIO_Label
RCC.HSE_VALUE=8000000
PB3.Mode=JTAG_5_pins
PA15.Mode=JTAG_5_pins
PB12.GPIO_Label=LCD_RS
PA1.GPIOParameters=GPIO_Label
PB4.Mode=JTAG_5_pins
PA14.Mode=JTAG_5_pins
PA0.Mode=IN1-Single-Ended
PC13.GPIO_PuPd=GPIO_PULLUP
PB7.Signal=GPIO_Output
PA8.Signal=S_TIM1_CH1
PB6.GPIOParameters=GPIO_Label
PA0.Signal=ADC1_IN1
PB7.GPIO_Label=SDA_PU
Mcu.Package=LQFP48
PB9.Signal=I2C1_SDA
PA2.GPIO_Label=CHB_TEMP
PA15.Signal=SYS_JTDI
PA5.GPIOParameters=GPIO_Label
PB14.GPIOParameters=GPIO_Label
PB13.Mode=Simplex_Bidirectional_Master
PA4.GPIO_Label=CHA_CUR
PB4.Signal=SYS_JTRST
PA3.Signal=ADC1_IN4
PA5.Mode=IN13-Single-Ended
PB8-BOOT0.Mode=I2C
PA7.Mode=Follower_Internally_Connected
PC13.Signal=GPXTI13
PA9.GPIO_Label=CHB_HI
PA11.GPIO_Label=CHA_LO
PA12.GPIO_Label=CHB_LO
PA3.Mode=IN4-Single-Ended
PA13.Signal=SYS_JTMS-SWDIO
PA8.GPIO_Label=CHA_HI
PB7.GPIOParameters=GPIO_Label
PB9.Mode=I2C
PA9.Signal=S_TIM1_CH2
PA1.Signal=ADC2_IN2
PB14.Signal=S_TIM15_CH1
PA5.Signal=ADC2_IN13
PB8-BOOT0.Signal=I2C1_SCL
board=custom
PB15.Mode=Simplex_Bidirectional_Master
PA1.Mode=IN2-Single-Ended
PB15.GPIO_Label=LCD_SDA (MOSI)
PC13.GPIOParameters=GPIO_PuPd,GPIO_Label,GPIO_ModeDefaultEXTI
PA1.GPIO_Label=CHB_CUR
PA4.GPIOParameters=GPIO_Label
PB15.GPIOParameters=GPIO_Label
PA13.Mode=JTAG_5_pins
Mcu.Name=STM32G431C(6-8-B)Tx
PA2.Signal=ADC1_IN3
PB3.Signal=SYS_JTDO-SWO
PA4.Signal=ADC2_IN17
RCC.SYSCLKFreq_VALUE=128000000
PA7.GPIO_Label=BAT_VOL
PA12.Mode=PWM Generation2 CH2 CH2N
PA5.GPIO_Label=CHA_TEMP
PC13.GPIO_ModeDefaultEXTI=GPIO_MODE_IT_FALLING
PA11.Signal=TIM1_CH1N
PA14.Signal=SYS_JTCK-SWCLK
PA0.GPIOParameters=GPIO_Label
PA2.Mode=IN3-Single-Ended
PA7.GPIOParameters=GPIO_Label
PB12.GPIOParameters=GPIO_Label
PB12.Signal=GPIO_Output
PA3.GPIO_Label=CHA_VOL
PA7.Signal=OPAMP1_VINP

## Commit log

2020-12-05 First commit of current work in progress
2020-12-05 Some temporary documentation while I get things in order.
2021-01-31 Some minor layout changes.
2021-05-06 Layout almost complete. Just needs a tidy.
2021-05-07 Remove some vias to prep for plugin stitching.
2021-05-16 Add stitching vias
2021-05-30 Produce manufacturing files
2021-05-30 Update .gitignore for manufacturing outputs
2021-05-30 Reflect current project status in README
2021-05-30 Add licensing information
2021-06-06 Update BOM * Datasheets * Manufacturers * Part numbers
2021-06-06 Update progress
2021-06-06 Ignore all manufacturing files
2021-08-22 Add I/O expander datasheet and HAL driver manual
    The PCAL6416A is used as an I/O expander, and we're using the HAL of the STM32
    micro. Both datasheets are useful for reference.
2021-08-22 Add FreeRTOS kernel as a submodule
2021-08-22 Update ignores to include STM32CubeIDE settings
2021-08-22 Rearrange firmware, and update licenses
2021-08-28 Create a basic firmware skeleton (#2)
    * Add FreeRTOS kernel as a submodule
    * Rearrange firmware, and update licenses
    * Update ignores to include STM32CubeIDE settings
2021-08-28 Finish initialisation of input module
2021-08-28 Started some work on the input I2C expander
2021-08-28 Add missing header for input module
2021-08-28 Flesh out the task a little more
2021-09-12 Start a transfer on interrupt
